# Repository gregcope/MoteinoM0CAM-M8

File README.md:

# MoteinoM0CAM-M8
A [Moteino M0](https://lowpowerlab.com/guide/moteino/moteinom0/) [Breakout board](https://lowpowerlab.com/guide/moteino/m0-sensor-shields/) for a uBlox [CAM-M8Q](https://www.u-blox.com/en/product/cam-m8-series) GNSS module.  This module has an integrated GNSS chip antenna.  The board also containers an MCP 1711 Low DropOut regulator to power the module from Moteino M0 VCC.  The battery backup (V_BCKP) is constantly powered by the Moteino M0 3.3v.

A green LED is connected to the TIMEPULSE output (1 pulse per second, synchronized at rising edge, pulse length 100 ms) as a visual fix indicator.

The LDO Enable pin (to power the main module down), TIMEPULSE and LNA Enable are connected to Moteino pins.

# Setup
* git clone https://github.com/u-blox/CadSoft-Eagle-Library and copy the ubloxLib.lbr to ~/Documents/eagle/libraries so that you have the CAM-M8Q part.

# BOM
* [CAM-M8Q - UK Link](https://www.tme.eu/gb/details/cam-m8q/gnss-gps-glonass-beidou-modules/u-blox)
* [Microchip Tech MCP1711T-33I/OT](https://lcsc.com/product-detail/Others_Microchip-Tech_MCP1711T-33I-OT_Microchip-Tech-MCP1711T-33I-OT_C79527.html)
* [0603 100nF SMD Capacitors](https://lcsc.com/product-detail/Multilayer-Ceramic-Capacitors-MLCC-SMD-SMT_Walsin-Tech-Corp-0603B104J250CT_C237171.html)
* [0603 4.7uF SMD Capacitor](https://lcsc.com/product-detail/Multilayer-Ceramic-Capacitors-MLCC-SMD-SMT_Walsin-Tech-Corp-0603N4R7C500CT_C314302.html)
* [0603 220 Ohm SMD Resistors](https://lcsc.com/product-detail/Chip-Resistor-Surface-Mount_Uniroyal-Elec-0603WAJ0221T5E_C1226.html)
* [0603 Green SMD LED](https://lcsc.com/product-detail/Light-Emitting-Diodes-LED_0603-green_C205443.html)

Design Notes
* Search the [CAM-M8 Hardware Integration Manual](https://www.u-blox.com/sites/default/files/CAM-M8-FW3_HardwareIntegrationManual_%28UBX-15030063%29.pdf) for the following referances:
* 220R Resitors on RXD and TXD as recommended here; 'To avoid interference by improperly shielded lines, it is recommended to use resistors' and section 2.2 'Minimal Design'
* 4.7uF from Section 2.2 'Minimal Design'
* The Regulator needs to supply 71mA max on CAM-8 startup (see 4.3 Indicative power requirements from the datasheet)
* Search the [MCP1711 Datasheet](https://datasheet.lcsc.com/szlcsc/Microchip-Tech-MCP1711T-33I-OT_C79527.pdf) for the following referances:
* The MCP1711 was chosen as it has an enable pin and low quiescent curent draw
* The 0.1uF input and output capacitor see 'For most applications, 0.1 µF of capacitance will ensure stable operation of the LDO circuit. If the output capacitor is used, the input capacitor should have a capacitance value equa' is from section 3.1 Unregulated Input Voltage(Vin)

# Other Resources
* Easyeda board: https://easyeda.com/granbobbi22/MAX-M8Q-Minimal-Breakout
* Watterott board: https://github.com/watterott/CAM-M8Q-Breakout/blob/master/hardware/CAM-M8Q-Breakout_v11.pdf
* CAM-M8u-blox M8 Data Sheet : https://www.u-blox.com/sites/default/files/CAM-M8-FW3_DataSheet_%28UBX-15031574%29.pdf
* CAM-M8 Hardware Integration Manual : https://www.u-blox.com/sites/default/files/CAM-M8-FW3_HardwareIntegrationManual_%28UBX-15030063%29.pdf
* MCP1711 Datasheet: https://datasheet.lcsc.com/szlcsc/Microchip-Tech-MCP1711T-33I-OT_C79527.pdf

# Schematic / Board

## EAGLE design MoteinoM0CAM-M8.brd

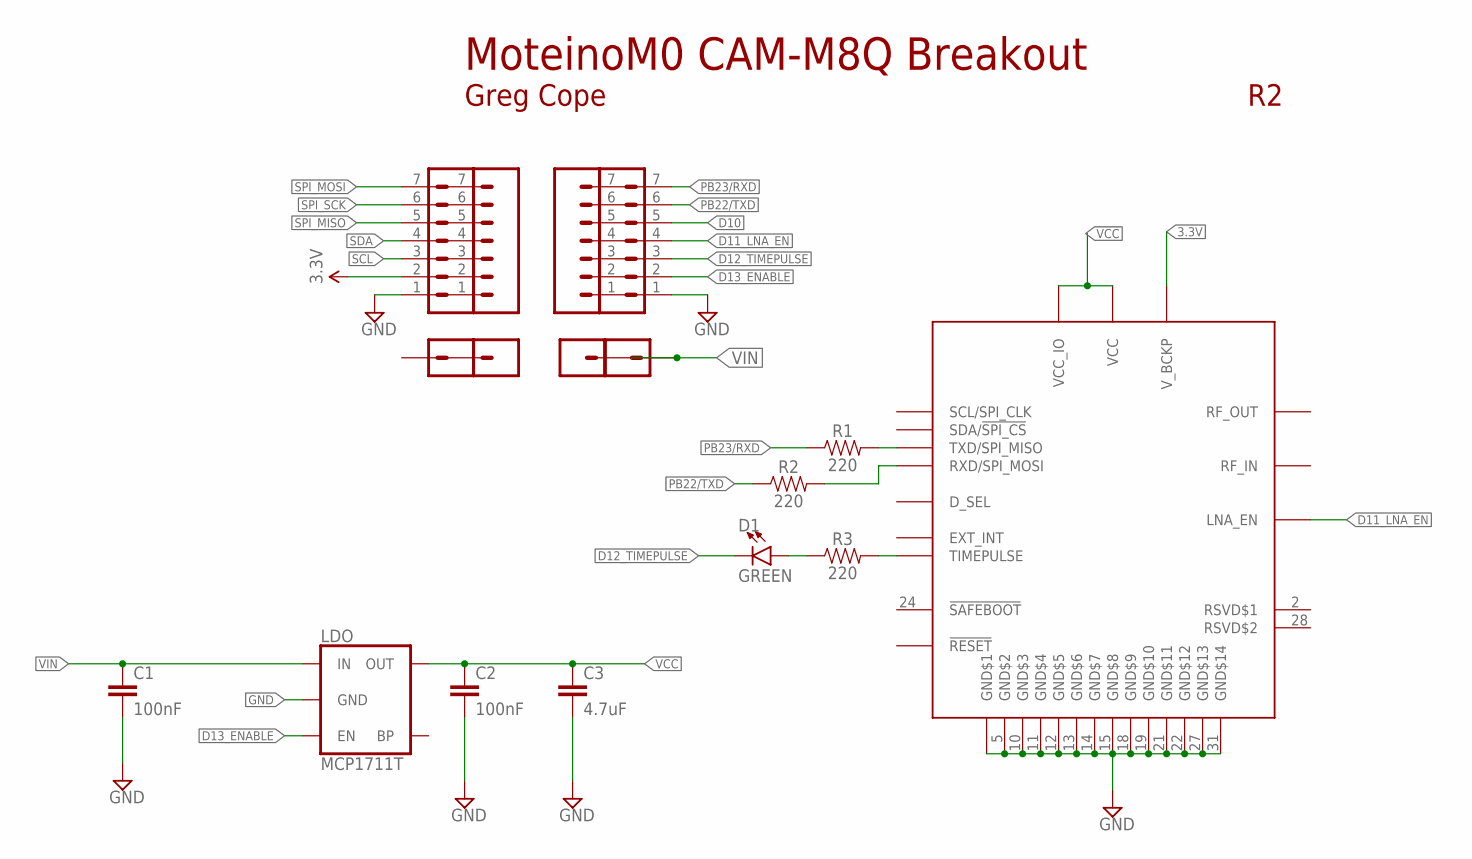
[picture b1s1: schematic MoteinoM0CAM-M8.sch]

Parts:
C1, C2: 100nF; 0603
C3: 4.7uF; 0603
D1: GREEN; LED-0603
J1, J2, J3, J4: CONN_01; 1X01
LDO: MCP1711T; SOT23-5
R1, R2, R3: 220; 0603
U$1: CAM-M8
U$4, U$10: HDR_7PINNS_THINRINGS; 1X07_NS_THINRINGS
U$17, U$18: HDR_7PINHH; 1X07_NS_THINRINGS_HH

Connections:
3.3V: U$1.8 (V_BCKP), U$18.2
D10: U$17.5
D11_LNA_EN: U$1.30 (LNA_EN), U$17.4
D12_TIMEPULSE: D1.C, U$17.3
D13_ENABLE: LDO.3 (EN), U$17.2
GND: C1.2, C2.2, C3.2, LDO.2 (GND), U$1.4 (GND$1), U$1.5 (GND$2), U$1.10 (GND$3), U$1.11 (GND$4), U$1.12 (GND$5), U$1.13 (GND$6), U$1.14 (GND$7), U$1.15 (GND$8), U$1.18 (GND$9), U$1.19 (GND$10), U$1.21 (GND$11), U$1.22 (GND$12), U$1.27 (GND$13), U$1.31 (GND$14), U$17.1, U$18.1
unnamed: R3.2, U$1.29 (TIMEPULSE)
unnamed: R1.2, U$1.25 (TXD/SPI_MISO)
unnamed: R2.2, U$1.26 (RXD/SPI_MOSI)
unnamed: D1.A, R3.1
PB22/TXD: R2.1, U$17.6
PB23/RXD: R1.1, U$17.7
SCL: U$18.3
SDA: U$18.4
SPI_MISO: U$18.5
SPI_MOSI: U$18.7
SPI_SCK: U$18.6
VCC: C2.1, C3.1, LDO.5 (OUT), U$1.1 (VCC_IO), U$1.9 (VCC)
VIN: C1.1, J3.1, J4.1, LDO.1 (IN)

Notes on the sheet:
Greg Cope
MoteinoM0 CAM-M8Q Breakout

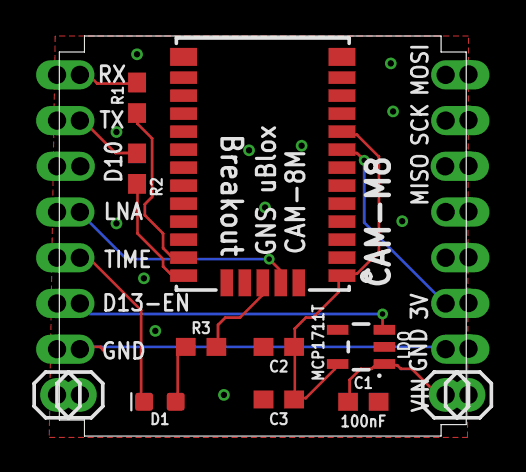
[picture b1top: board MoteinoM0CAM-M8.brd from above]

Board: 2 copper layers, 22.6 x 22.2 mm, 17 parts (1 on the bottom side), 13 nets.

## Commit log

2019-06-16 inital commit
2019-06-17 update readme, GND plane
2019-06-18 added another header bodge
2019-06-22 Added resistors, led and capacitors
2019-06-24 Doco update
2019-06-24 Doco update II
2019-06-24 Doco update III
2019-06-24 Doco update IV
2019-06-24 Added images
2019-06-24 update images
2019-06-25 added vias
2019-06-25 added doco
2019-06-28 added resource
2019-07-01 Connection tidy, layout tweaks
2019-07-01 new images
2019-08-04 updates II
2019-08-04 updates III
2019-08-04 updates IIII
2019-08-04 updates IIIII
2019-08-04 moved 4.7uF
2019-08-04 final
2019-08-04 final III
2019-08-18 Corrected 1203 to 0603 LED

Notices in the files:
parts and their libraries:
SparkFun-Connectors: Licensing: Creative Commons ShareAlike 4.0 International - https://creativecommons.org/licenses/by-sa/4.0
SparkFun-Aesthetics: Licensing: CC v3.0 Share-Alike You are welcome to use this library for commercial purposes.
